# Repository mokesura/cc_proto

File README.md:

# CC Proto

CC Protoは、リバーシブル設計の18キーのキーボードです。

## 特徴
CC Protoは、以下の特徴を持っています。

- リバーシブル設計
- マイコンにPro Microを使用。コンスルーによる抜き差しに対応。
- Cherry MX互換/Kailh Choc V1/Kailh Mid-Height/ALPS系スイッチ対応
  - Cherry MX互換/Kailh Mid-HeightスイッチはKailhソケットとはんだ付けの両方に対応。その他スイッチははんだ付けのみに対応。
  - Rev.3よりKailh Choc V2に対応。ただし、Rev.3ではスイッチの固定用足を切断する必要あり。Rev.4以降はスイッチの加工なしで取り付けができます。
  - 動作確認はCherry MX互換/Kailh Mid-Heightスイッチのみ。
- QMK Firmware対応
- [Remap](https://remap-keys.app)でのキーマップ変更に対応（VIAは動作未確認）
- LED（SK6812MINI）によるレイヤーの色分け表示（使用中ほとんど見えません）

## 組み立て済みキーボードを手にした方向けの利用ガイド
千葉千夏から組み立て済みのキーボードを受け取った方は、以下のページをご覧ください。

- [「CC Proto」組み立て済みキーボードを手にした方向けの利用ガイド](https://github.com/mokesura/cc_proto/blob/main/doc/0_guide_for_prepared_keyboard.md)

## ファームウェア
編集中につき、内容がコロコロ変わります。デフォルトファームウェアはRemap/VIA対応です。

- [Hex File](https://github.com/mokesura/cc_proto/tree/main/firmware)
- [QMK Firmware Sources](https://github.com/mokesura/qmk_firmware/tree/mokesura/cc_proto/keyboards/mokesura/cc_proto)

## キーボードの入手方法
自分用（というか、知り合いに使ってみてもらう用）に作成したキーボードですが、余った基板を頒布するかもしれません。  
ビルドガイドの作成予定は、今のところありません。

### PCB Data / Plate Data
KiCadで作成した基板データ、ガーバーデータを公開しています。

- [PCB Data](https://github.com/mokesura/cc_proto/tree/main/pcb) 
- [Top Plate Data](https://github.com/mokesura/cc_proto/tree/main/pcb_top) 

## 回路図
- [回路図/Schematic](https://github.com/mokesura/cc_proto/blob/main/pcb/cc_proto-Schematic.pdf)

## 組み立てに必要な部品リスト

### 基板

- PCB×1
- ボトムプレート×1（データ未作成。PCBで代用可）
- トッププレート×1（必要に応じて使用、Kailh Mid-Height/ALPS系スイッチには非対応）

### 基板以外の部品

- Pro Micro×1
- 12pin コンスルー×2（必要に応じて）
- ダイオード（1N4148または1N4148W）×18
- SK6812MINI×1（オプション）
- Kailh MX スイッチソケット×18（必要に応じて。Cherry MX互換/Kailh Mid-Heightスイッチのみ対応）
- タクトスイッチ（3.5x6.0x4.3mmのもの） ×1（Pro Microが露出している構造のため、RSTとGNDをショートさせることで代用可能）
- キースイッチ×18（Cherry MX互換/Kailh Choc V1/Kailh Choc V2/Kailh Mid-Height/ALPS系に対応。一応、混ぜても使用できますが、トッププレート使用時には工夫が必要です）
- キーキャップ×18（キースイッチに対応したもの）
- M2スペーサー、M2ネジ
  - PCBにはネジ穴が5つ開いてますが、中央を除いた4つをネジ止めすれば問題ないと思います（トッププレートは、ネジ穴4つのデータを公開しています）。
  - スペーサーの長さは使用するスイッチによって異なります。Cherry MX互換スイッチ使用の場合、M2スペーサー3.5mm×8、M2ネジ8mm×4、M2ネジ3mm×4で組み立てしています。
- ゴム脚（好みの大きさのもの）×4

## ライセンス
[MIT License](https://github.com/mokesura/cc_proto/blob/main/LICENSE)

## 使用したKiCadフットプリント
- [cc_proto.pretty](https://github.com/mokesura/cc_proto/tree/main/pcb/cc_proto.pretty) MIT Licenseのものを改変して利用。
- [KBD - for building keyboard libraries](https://github.com/foostan/kbd) 改変元。

## 連絡先
- 千葉千夏 / Chinatsu Chiba (azulee/mokesura)
  - Twitter: [@azulee](https://twitter.com/azulee)
  - E-Mail: mokesura@gmail.com

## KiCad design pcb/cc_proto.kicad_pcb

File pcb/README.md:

# CC Proto - PCB

## Front Side

## Back Side

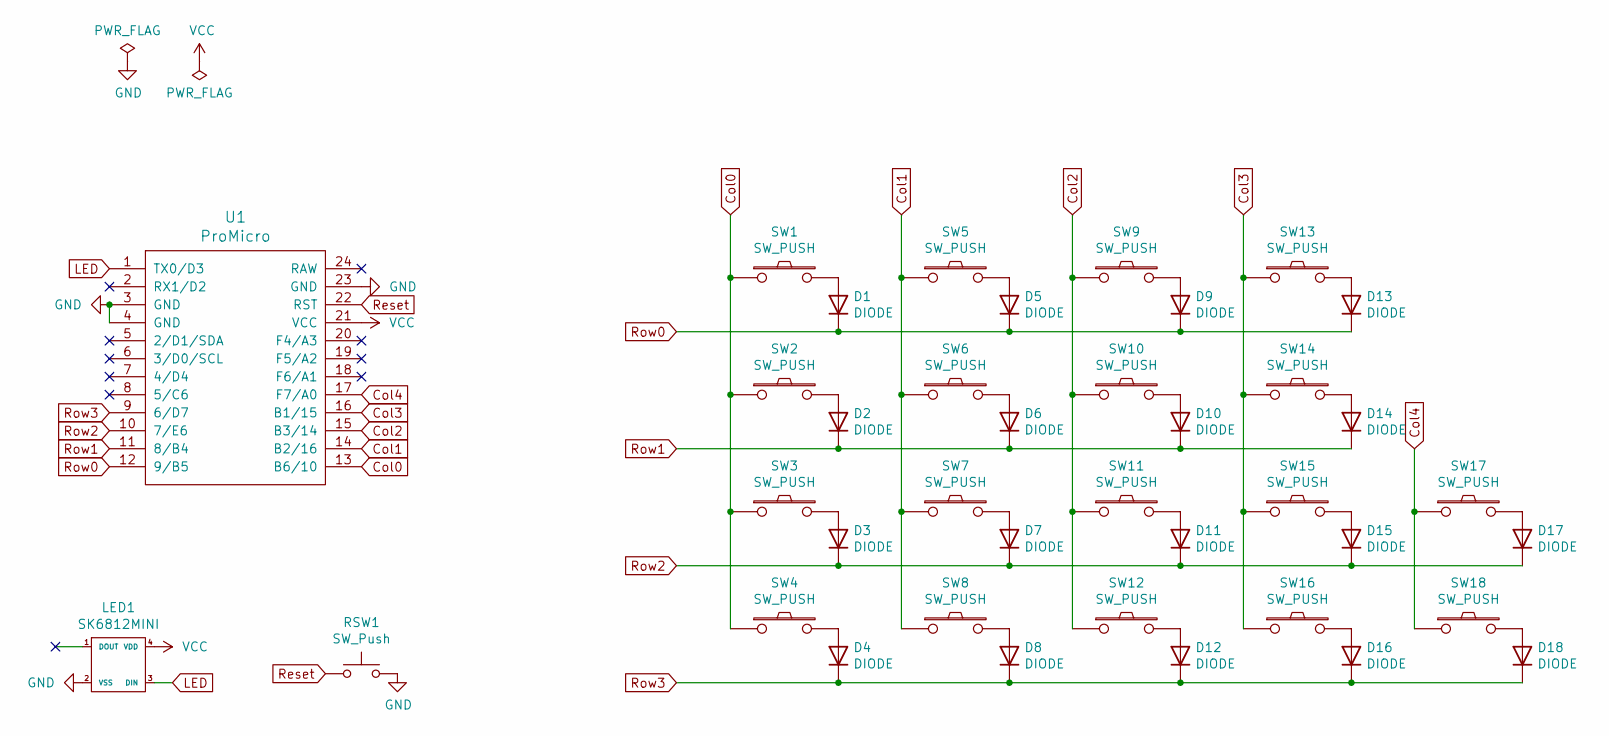
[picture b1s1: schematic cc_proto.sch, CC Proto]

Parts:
D1, D2, D3, D4, D5, D6, D7, D8, D9, D10, D11, D12, D13, D14, D15, D16, D17, D18: DIODE; D3_TH_SMD_Text-Added
LED1: SK6812MINI; SK6812MINI_rev_Text-Added
RSW1: SW_Push; ResetSW
SW1, SW2, SW3, SW4, SW5, SW6, SW7, SW8, SW9, SW10, SW11, SW12, SW13, SW14, SW15, SW16, SW17, SW18: SW_PUSH; CherryMX_MidHeight_Hotswap_Choc12_Alps_v2
U1: ProMicro; ProMicro_v2_Text-Changed

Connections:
Col0: SW1.1, SW2.1, SW3.1, SW4.1, U1.13 (B6/10)
Col1: SW5.1, SW6.1, SW7.1, SW8.1, U1.14 (B2/16)
Col2: SW9.1, SW10.1, SW11.1, SW12.1, U1.15 (B3/14)
Col3: SW13.1, SW14.1, SW15.1, SW16.1, U1.16 (B1/15)
Col4: SW17.1, SW18.1, U1.17 (F7/A0)
GND: LED1.2 (VSS), RSW1.2, U1.3 (GND), U1.4 (GND), U1.23 (GND)
LED: LED1.3 (DIN), U1.1 (TX0/D3)
unnamed: D1.2 (A), SW1.2
unnamed: D2.2 (A), SW2.2
unnamed: D3.2 (A), SW3.2
unnamed: D4.2 (A), SW4.2
unnamed: D5.2 (A), SW5.2
unnamed: D6.2 (A), SW6.2
unnamed: D7.2 (A), SW7.2
unnamed: D8.2 (A), SW8.2
unnamed: D9.2 (A), SW9.2
unnamed: D10.2 (A), SW10.2
unnamed: D11.2 (A), SW11.2
unnamed: D12.2 (A), SW12.2
unnamed: D13.2 (A), SW13.2
unnamed: D14.2 (A), SW14.2
unnamed: D15.2 (A), SW15.2
unnamed: D16.2 (A), SW16.2
unnamed: D17.2 (A), SW17.2
unnamed: D18.2 (A), SW18.2
Reset: RSW1.1, U1.22 (RST)
Row0: D1.1 (K), D5.1 (K), D9.1 (K), D13.1 (K), U1.12 (9/B5)
Row1: D2.1 (K), D6.1 (K), D10.1 (K), D14.1 (K), U1.11 (8/B4)
Row2: D3.1 (K), D7.1 (K), D11.1 (K), D15.1 (K), D17.1 (K), U1.10 (7/E6)
Row3: D4.1 (K), D8.1 (K), D12.1 (K), D16.1 (K), D18.1 (K), U1.9 (6/D7)
VCC: LED1.4 (VDD), U1.21 (VCC)

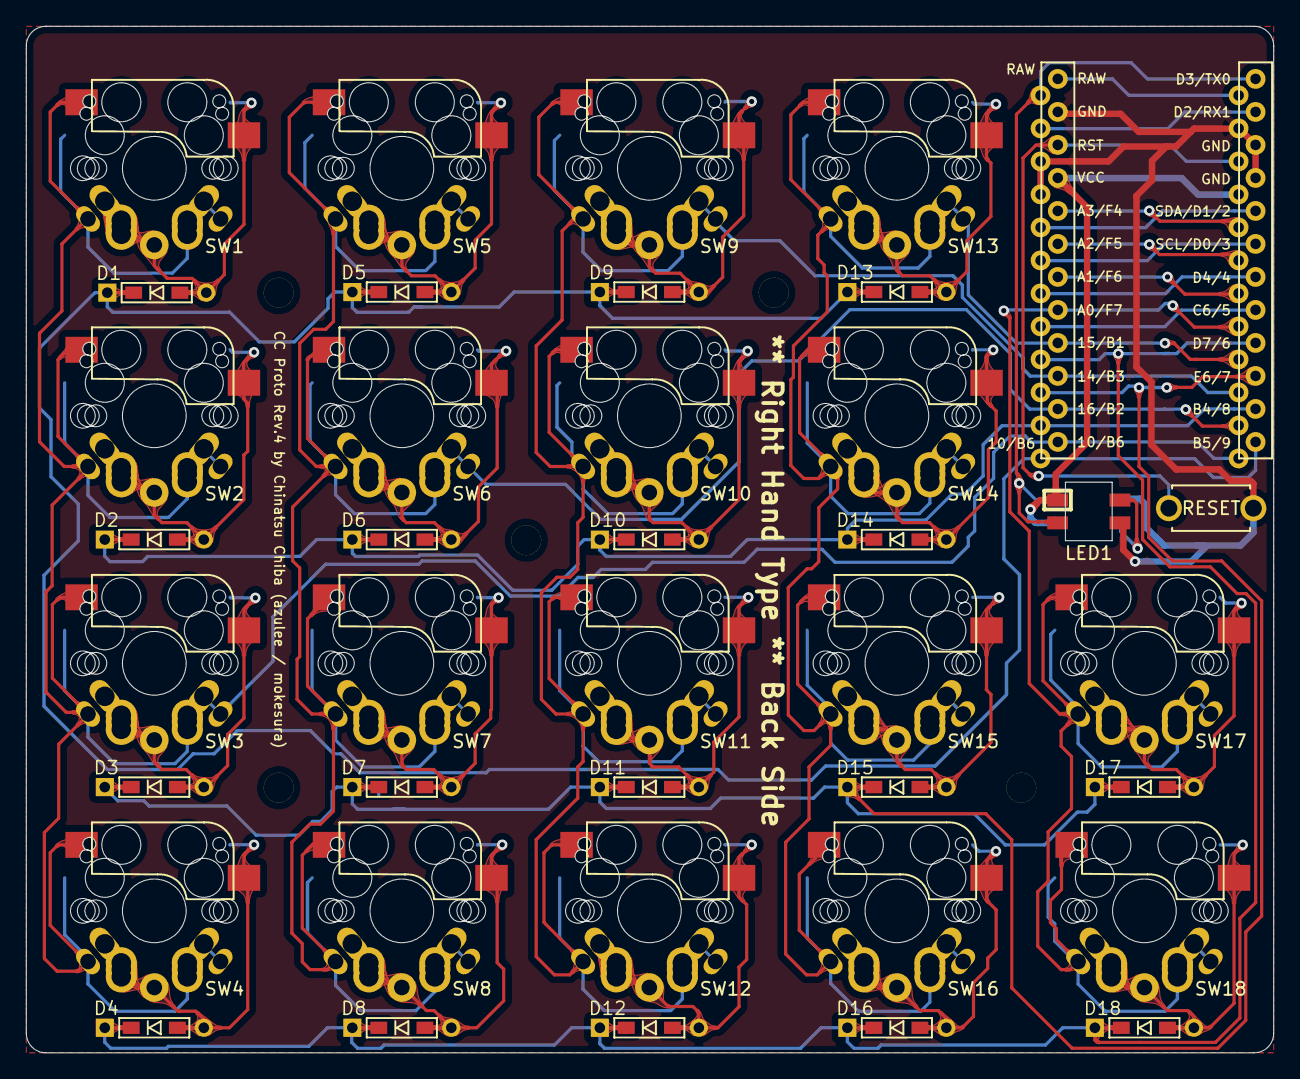
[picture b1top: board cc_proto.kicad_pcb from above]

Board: 2 copper layers, 96.0 x 79.0 mm, 44 parts (0 on the bottom side), 31 nets.

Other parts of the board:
Ref**: Val**; M2_Threads_v2
Ref**#2, Ref**#3, Ref**#4, Ref**#5: Val**; M2_Threads_v2

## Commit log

2021-07-07 権利者名変更
2021-07-09 フォルダ移動
2021-07-09 upload
2021-07-19 Readme作成
2021-07-21 回路図公開
2021-07-22 add files
2021-07-22 PCB Rev.3
2021-08-10 build by QMK Firmware 0.13.33
2021-08-15 Changed LED color
2021-08-15 PCB Rev.4
2021-08-15 Choc V2スイッチとPCB Rev.4について言及
2021-09-11 ガーバーファイルのファイル名変更
2021-09-11 plate-top Rev.2
2021-09-11 pcb_top Rev.2
2021-09-11 トッププレートデータ公開
2021-09-11 pcb image upload
